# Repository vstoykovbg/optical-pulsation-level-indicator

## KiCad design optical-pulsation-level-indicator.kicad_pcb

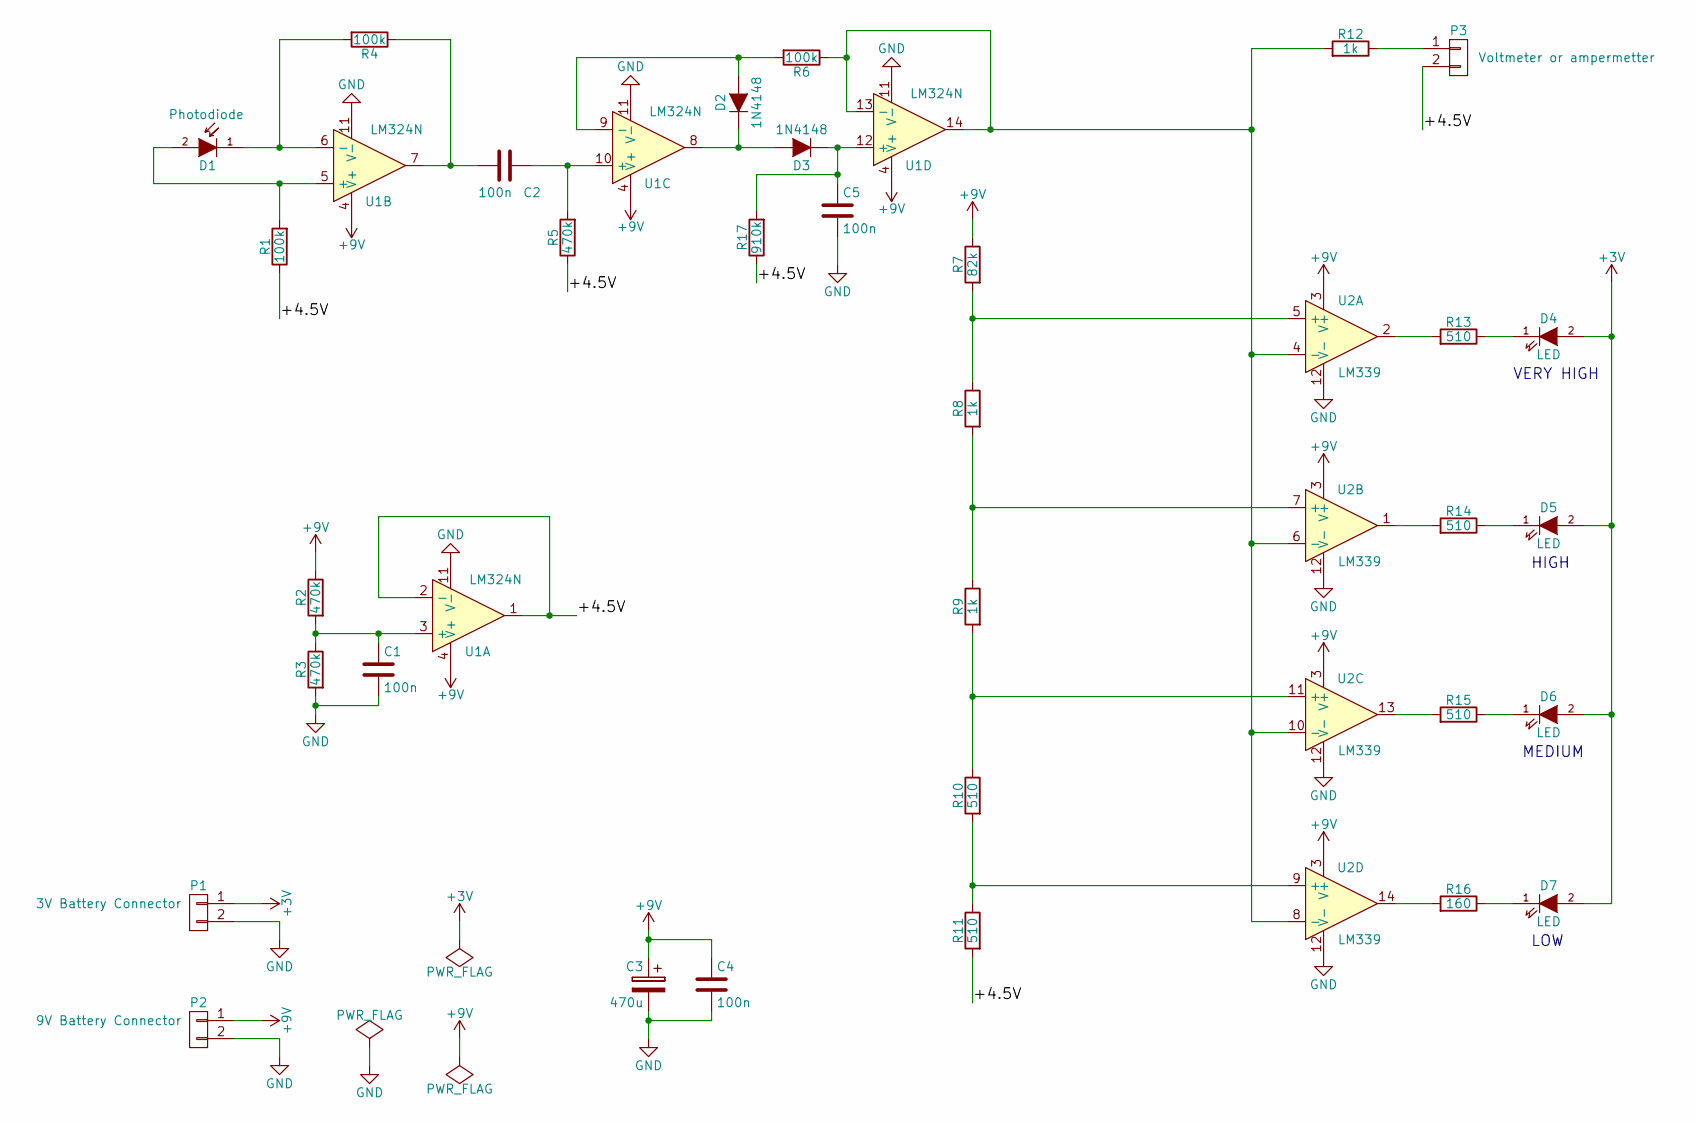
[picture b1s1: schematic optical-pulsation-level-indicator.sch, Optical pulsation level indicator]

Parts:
C1, C2, C4, C5: 100n; C_Rect_L7_W2.5_P5
C3: 470u; C_Radial_D8_L21_P3.8
D1: Photodiode; LED-5MM
D2, D3: 1N4148; Diode_DO-35_SOD27_Horizontal_RM10
D4, D5, D6, D7: LED; LED-5MM
P1: 3V Battery Connector; Battery_Connector
P2: 9V Battery Connector; Battery_Connector
P3: Voltmeter or ampermetter; Voltmeter_Connector
R1, R4, R6: 100k; Resistor_Horizontal_RM15mm
R2, R3, R5: 470k; Resistor_Horizontal_RM15mm
R7: 82k; Resistor_Horizontal_RM15mm
R8, R9, R12: 1k; Resistor_Horizontal_RM15mm
R10, R11, R13, R14, R15: 510; Resistor_Horizontal_RM15mm
R16: 160; Resistor_Horizontal_RM15mm
R17: 910k; Resistor_Horizontal_RM15mm
U1: LM324N; DIP-14_W7.62mm_LongPads
U2: LM339; DIP-14_W7.62mm_LongPads

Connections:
+3V: D4.2 (A), D5.2 (A), D6.2 (A), D7.2 (A), P1.1
+9V: C3.1, C4.1, P2.1, R2.1, R7.1, U1.4 (V+), U2.3 (V+)
/+4.5V: P3.2, R1.1, R5.1, R11.2, R17.1, U1.1, U1.2 (-)
GND: C1.2, C3.2, C4.2, C5.2, P1.2, P2.2, R3.2, U1.11 (V-), U2.12 (V-)
unnamed: C1.1, R2.2, R3.1, U1.3 (+)
unnamed: C2.1, R5.2, U1.10 (+)
unnamed: C2.2, R4.1, U1.7
unnamed: C5.1, D3.1 (K), R17.2, U1.12 (+)
unnamed: D1.1 (K), R4.2, U1.6 (-)
unnamed: D1.2 (A), R1.2, U1.5 (+)
unnamed: D2.1 (K), D3.2 (A), U1.8
unnamed: D2.2 (A), R6.2, U1.9 (-)
unnamed: D4.1 (K), R13.1
unnamed: D5.1 (K), R14.1
unnamed: D6.1 (K), R15.1
unnamed: D7.1 (K), R16.1
unnamed: P3.1, R12.1
unnamed: R7.2, R8.1, U2.5 (+)
unnamed: R8.2, R9.1, U2.7 (+)
unnamed: R9.2, R10.1, U2.11 (+)
unnamed: R10.2, R11.1, U2.9 (+)
unnamed: R6.1, R12.2, U1.13 (-), U1.14, U2.4 (-), U2.6 (-), U2.8 (-), U2.10 (-)
unnamed: R13.2, U2.2
unnamed: R14.2, U2.1
unnamed: R15.2, U2.13
unnamed: R16.2, U2.14

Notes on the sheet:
LOW
MEDIUM
HIGH
VERY HIGH

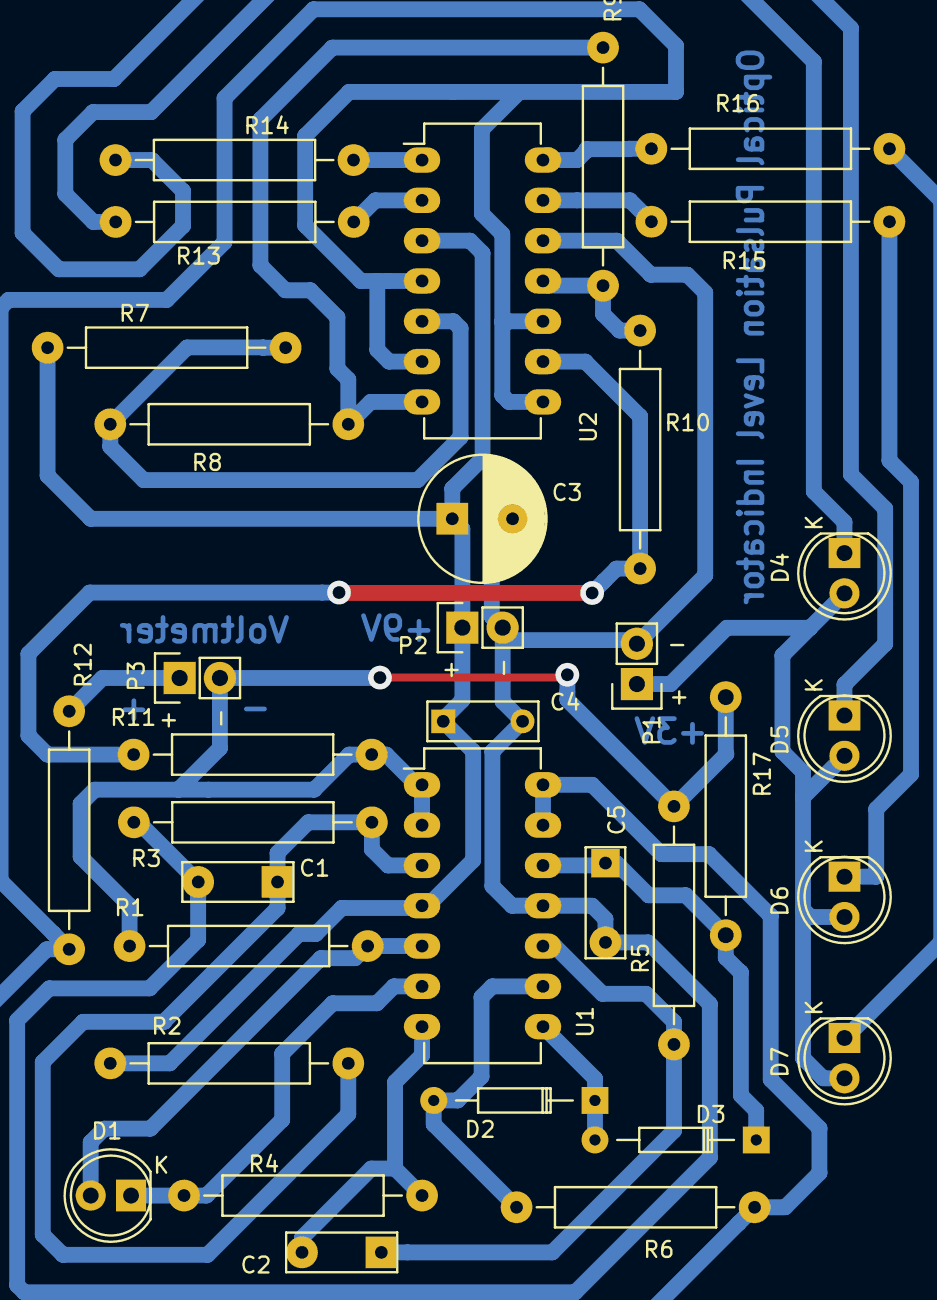
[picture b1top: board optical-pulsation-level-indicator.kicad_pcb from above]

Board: 2 copper layers, 34 parts (0 on the bottom side), 26 nets.

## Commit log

2017-07-28 New KiCad version, pdf, screnshots
2022-01-22 Create Sjenica1
    Authorized mit meine Account Sjenica1 github.com reufrujevic750@gmail.com
